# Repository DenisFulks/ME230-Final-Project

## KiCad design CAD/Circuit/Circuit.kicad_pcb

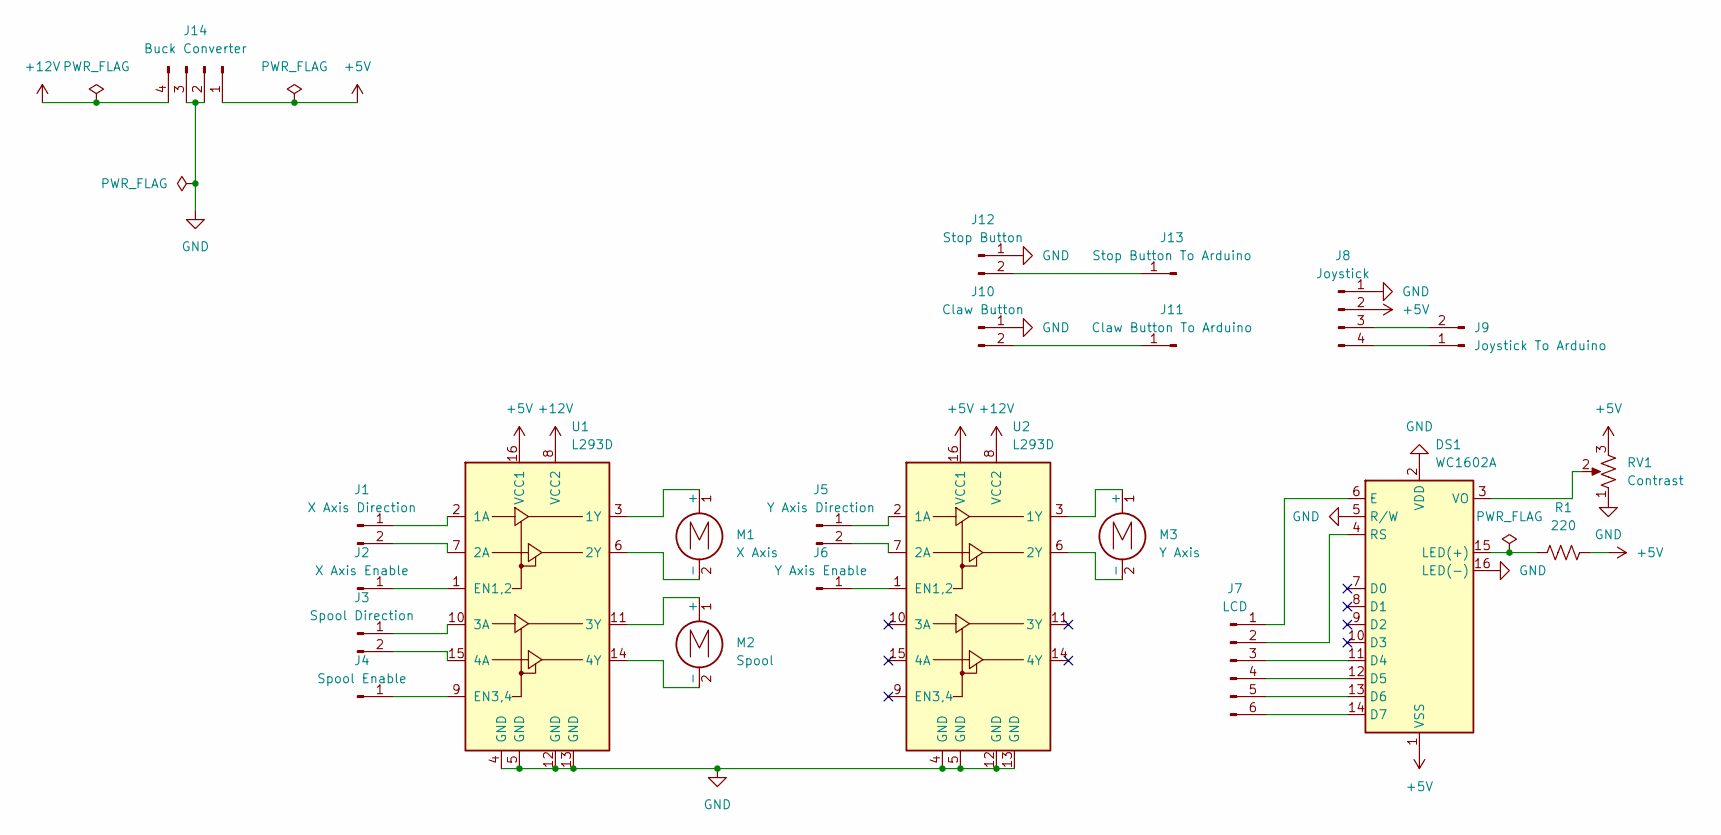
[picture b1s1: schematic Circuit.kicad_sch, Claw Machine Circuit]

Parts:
DS1: WC1602A
J1: X Axis Direction; PinHeader_1x02_P1.00mm_Vertical
J2: X Axis Enable; PinHeader_1x01_P1.00mm_Vertical
J3: Spool Direction; PinHeader_1x02_P1.00mm_Vertical
J4: Spool Enable; PinHeader_1x01_P1.00mm_Vertical
J5: Y Axis Direction; PinHeader_1x02_P1.00mm_Vertical
J6: Y Axis Enable; PinHeader_1x01_P1.00mm_Vertical
J7: LCD; PinHeader_1x06_P1.00mm_Vertical
J8: Joystick; PinHeader_1x04_P1.00mm_Vertical
J9: Joystick To Arduino; PinHeader_1x02_P1.00mm_Vertical
J10: Claw Button; PinHeader_1x02_P1.00mm_Vertical
J11: Claw Button To Arduino; PinHeader_1x01_P1.00mm_Vertical
J12: Stop Button; PinHeader_1x02_P1.00mm_Vertical
J13: Stop Button To Arduino; PinHeader_1x01_P1.00mm_Vertical
J14: Buck Converter; PinHeader_1x04_P1.00mm_Vertical
M1: X Axis; PinHeader_1x02_P1.00mm_Vertical
M2: Spool; PinHeader_1x02_P1.00mm_Vertical
M3: Y Axis; PinHeader_1x02_P1.00mm_Vertical
R1: 220; R_Axial_DIN0309_L9.0mm_D3.2mm_P12.70mm_Horizontal
RV1: Contrast; Potentiometer_Bourns_3266W_Vertical
U1, U2: L293D; DIP-16_W7.62mm

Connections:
+5V: DS1.1 (VSS), J8.2, J14.1, R1.2, RV1.3, U1.16 (VCC1), U2.16 (VCC1)
+12V: J14.4, U1.8 (VCC2), U2.8 (VCC2)
GND: DS1.2 (VDD), DS1.5 (R/W), DS1.16 (LED(-)), J8.1, J10.1, J12.1, J14.2, J14.3, RV1.1, U1.4 (GND), U1.5 (GND), U1.12 (GND), U1.13 (GND), U2.4 (GND), U2.5 (GND), U2.12 (GND), U2.13 (GND)
unnamed: DS1.11 (D4), J7.3
unnamed: DS1.12 (D5), J7.4
unnamed: DS1.13 (D6), J7.5
unnamed: DS1.14 (D7), J7.6
unnamed: DS1.6 (E), J7.1
unnamed: DS1.15 (LED(+)), R1.1
unnamed: DS1.4 (RS), J7.2
unnamed: DS1.3 (VO), RV1.2
unnamed: J1.1, U1.2 (1A)
unnamed: J1.2, U1.7 (2A)
unnamed: J2.1, U1.1 (EN1,2)
unnamed: J3.1, U1.10 (3A)
unnamed: J3.2, U1.15 (4A)
unnamed: J4.1, U1.9 (EN3,4)
unnamed: J5.1, U2.2 (1A)
unnamed: J5.2, U2.7 (2A)
unnamed: J6.1, U2.1 (EN1,2)
unnamed: J8.3, J9.2
unnamed: J8.4, J9.1
unnamed: J10.2, J11.1
unnamed: J12.2, J13.1
unnamed: M1.1 (+), U1.3 (1Y)
unnamed: M1.2 (-), U1.6 (2Y)
unnamed: M2.1 (+), U1.11 (3Y)
unnamed: M2.2 (-), U1.14 (4Y)
unnamed: M3.1 (+), U2.3 (1Y)
unnamed: M3.2 (-), U2.6 (2Y)

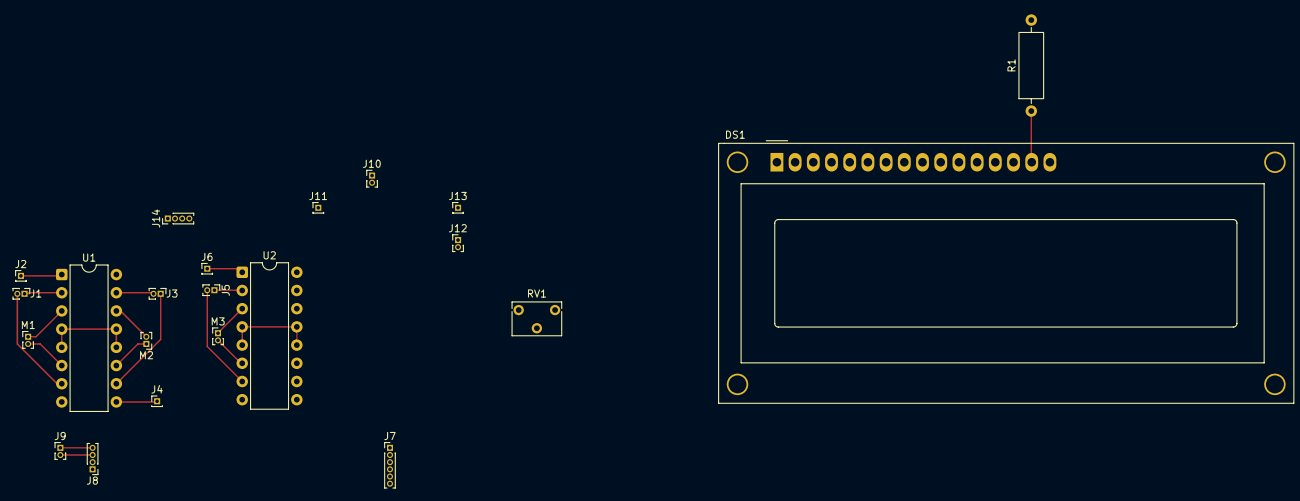
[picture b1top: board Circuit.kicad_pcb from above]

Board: 2 copper layers, 22 parts (0 on the bottom side), 30 nets.

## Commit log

2025-12-11 Reorganization
2025-12-16 More CAD
2026-01-05 Working on CAD
2026-01-06 Working on Pulley
2026-01-06 Still Working on Pulley, Almost done with Major
2026-01-06 Checking Pulley Length, Should be Good to Go
2026-01-07 Major Gantry Should be Done
2026-01-12 Working on Minor Pulley
2026-01-12 Claw
2026-01-12 Servo motor
2026-01-12 Added Hardware
2026-01-13 Working on Claw
2026-01-14 Reorganized and Renamed
2026-01-15 Servo Connector Edit
2026-01-15 Servo Connector Work
2026-01-18 Making Cut List
2026-01-18 Claw Code
2026-01-20 Modifying Gantry Slides
2026-01-20 Test
2026-01-20 Servo Rudder
2026-01-21 Working on Major Pulley:
2026-01-24 Spool Creation
2026-01-24 Working
2026-01-24 Working on Minor Gantry
2026-01-27 Working So Far
2026-01-29 Working on Console
2026-01-29 Fixing Things
2026-01-29 Console Work
2026-01-29 Transitioning to new motors
2026-01-30 Motors
2026-02-03 Code
2026-02-03 CAD Hopefully Finished
2026-02-03 Coin Slot
2026-02-08 LCD Mount
2026-02-08 Working on Code
2026-02-09 Working on Code. Still Need to Add Coin Slot and LCD
2026-02-16 Hopefully Done
